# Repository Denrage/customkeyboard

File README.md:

# Custom Keyboard
## Planned Features
- ISO-Layout
- RGB per Key
- RGB Underglow
- TKL (80%)
- USB-C
- QMK
## Ressources
- JLCPCB - PCB Manfucaturer
- http://www.keyboard-layout-editor.com/#/
- https://github.com/jeroen94704/klepcbgen
- https://wiki.ai03.com/books/pcb-design/page/pcb-guide-part-1---preparations
- https://github.com/ruiqimao/keyboard-pcb-guide
## Needed Components (Will be more specific in the future)
- Resistors
- Diodes
- Key Switches
- (Key Caps)
- MCU
- Crystal/Clock
- USB-C Port
- RGB-LEDs
## Needed Tools
- Soldering Iron
- Soldering Paste
- Solder
- Hot Air Gun
- Flux
- Magnifying glass / microscope
- Fan

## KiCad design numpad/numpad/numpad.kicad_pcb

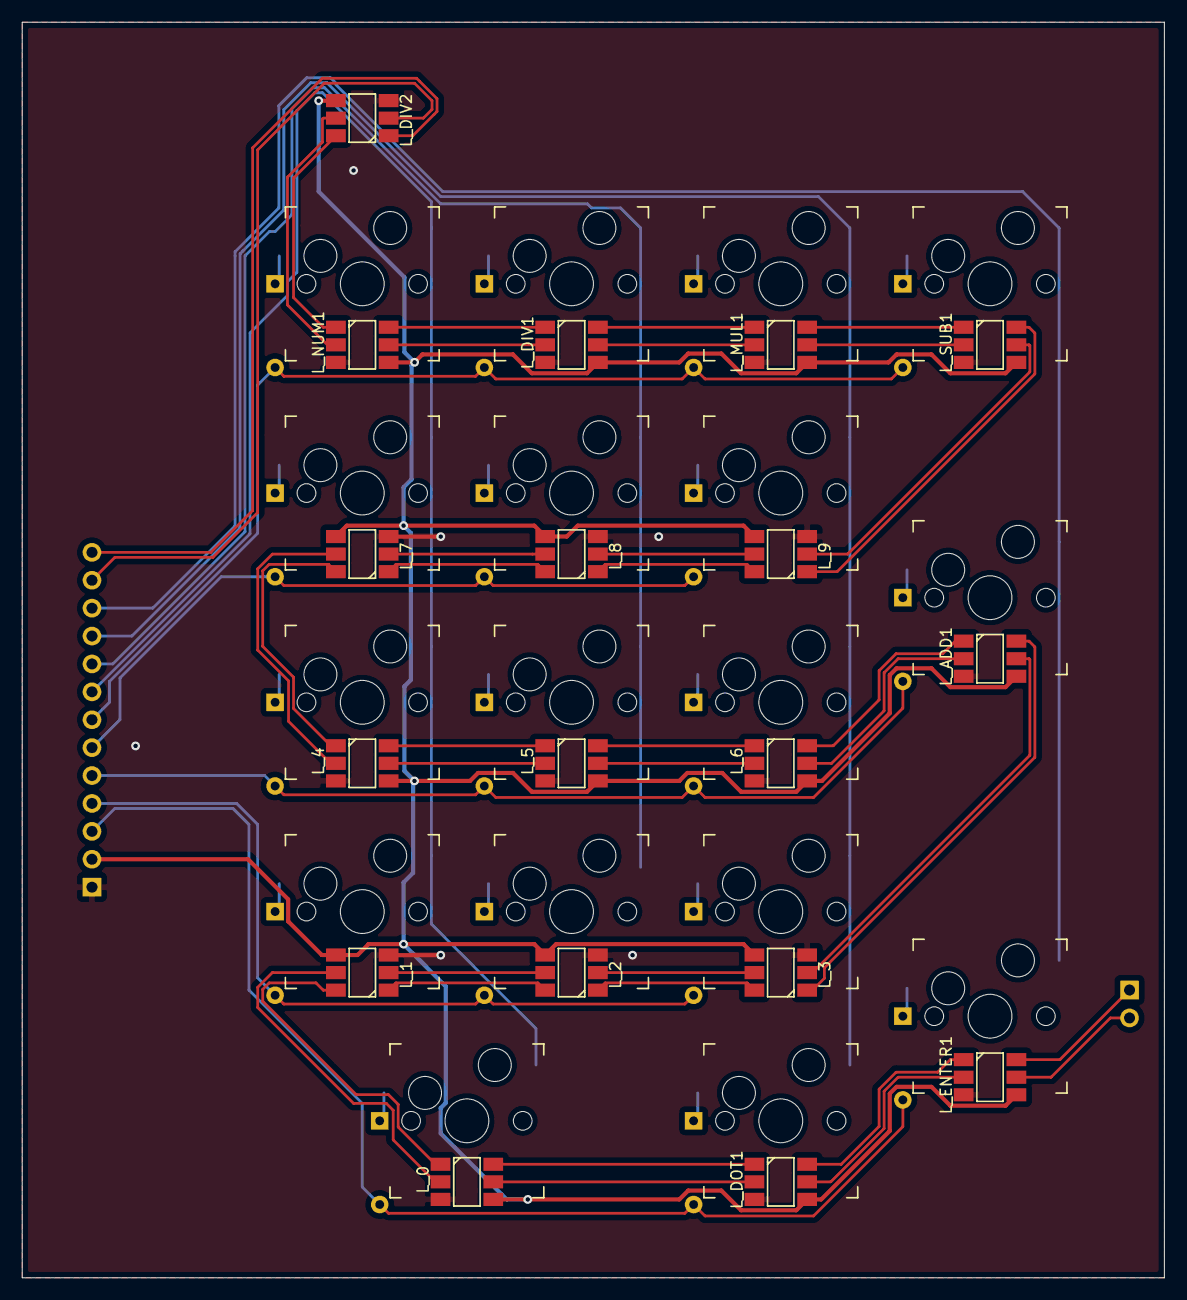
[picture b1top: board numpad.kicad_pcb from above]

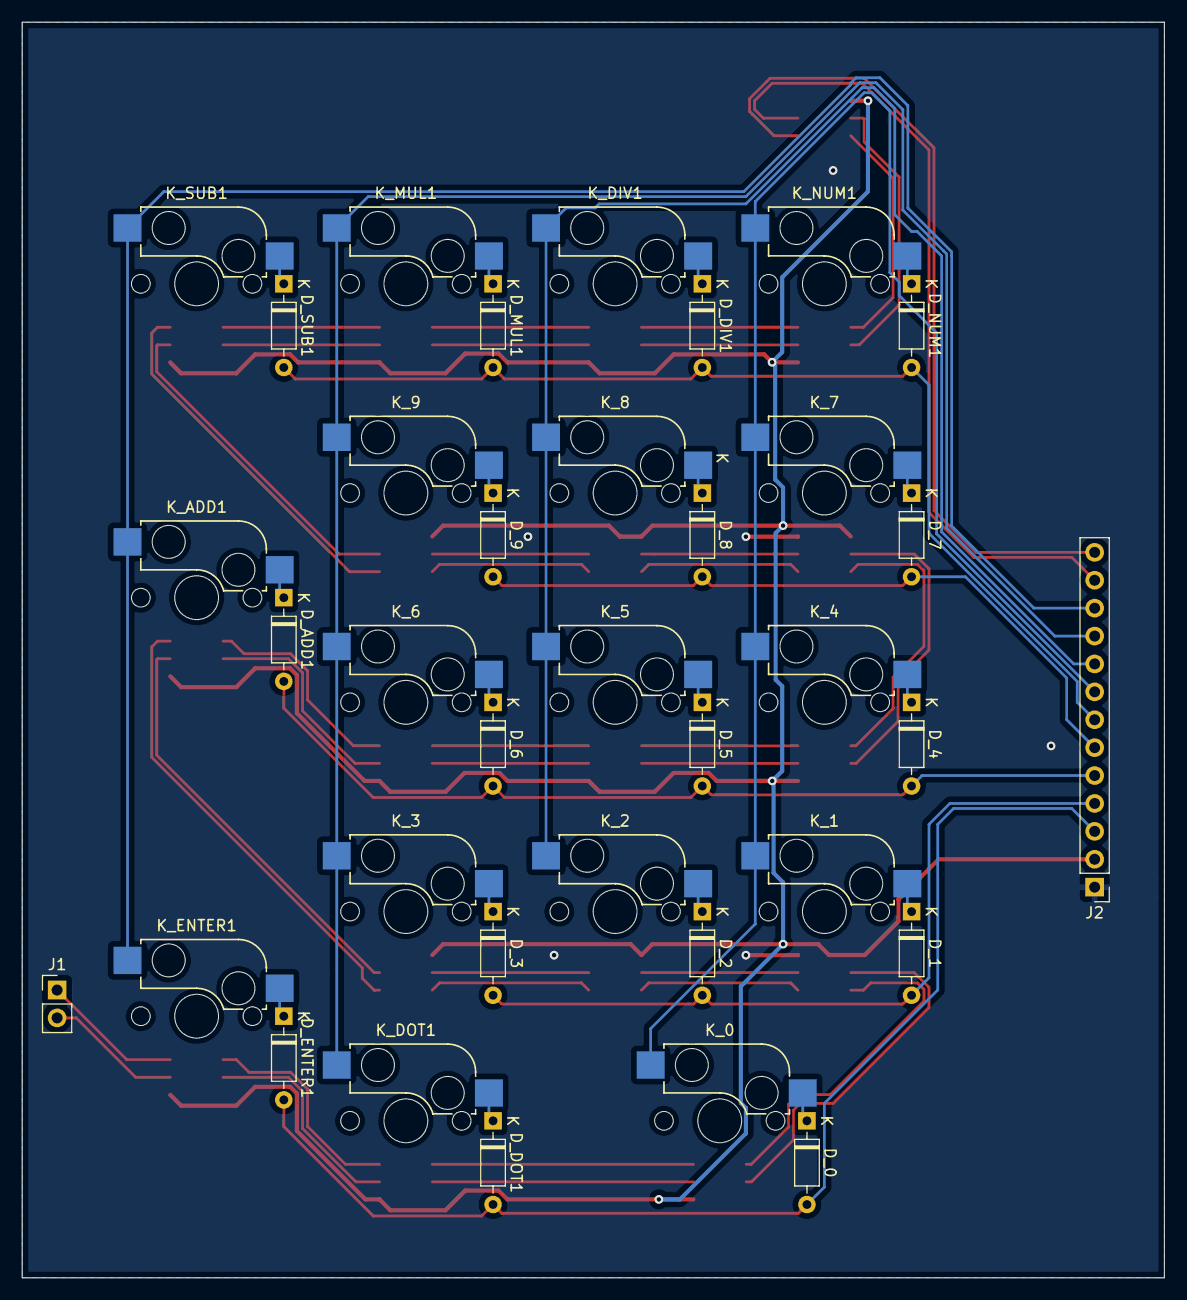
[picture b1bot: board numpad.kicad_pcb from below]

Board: 2 copper layers, 104.0 x 114.3 mm, 54 parts (19 on the bottom side), 66 nets.

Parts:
D_0, D_1, D_2, D_3, D_4, D_5, D_6, D_7, D_8, D_9: DIODE; D_DO-35_SOD27_P7.62mm_Horizontal
D_ADD1: DIODE; D_DO-35_SOD27_P7.62mm_Horizontal
D_DIV1: DIODE; D_DO-35_SOD27_P7.62mm_Horizontal
D_DOT1: DIODE; D_DO-35_SOD27_P7.62mm_Horizontal
D_ENTER1: DIODE; D_DO-35_SOD27_P7.62mm_Horizontal
D_MUL1: DIODE; D_DO-35_SOD27_P7.62mm_Horizontal
D_NUM1: DIODE; D_DO-35_SOD27_P7.62mm_Horizontal
D_SUB1: DIODE; D_DO-35_SOD27_P7.62mm_Horizontal
J1: Conn_01x02; PinHeader_1x02_P2.54mm_Vertical
J2: Conn_01x13; PinHeader_1x13_P2.54mm_Vertical
K_0, K_1, K_2, K_3, K_4, K_5, K_6, K_7, K_8, K_9: SW_DIP_x01; Kailh_socket_MX
K_ADD1: SW_DIP_x01; Kailh_socket_MX
K_DIV1: SW_DIP_x01; Kailh_socket_MX
K_DOT1: SW_DIP_x01; Kailh_socket_MX
K_ENTER1: SW_DIP_x01; Kailh_socket_MX
K_MUL1: SW_DIP_x01; Kailh_socket_MX
K_NUM1: SW_DIP_x01; Kailh_socket_MX
K_SUB1: SW_DIP_x01; Kailh_socket_MX
L_0, L_1, L_2, L_3, L_4, L_5, L_6, L_7, L_8, L_9: SK9822; APA102_hand_solder
L_ADD1: SK9822; APA102_hand_solder
L_DIV1, L_DIV2: SK9822; APA102_hand_solder
L_DOT1: SK9822; APA102_hand_solder
L_ENTER1: SK9822; APA102_hand_solder
L_MUL1: SK9822; APA102_hand_solder
L_NUM1: SK9822; APA102_hand_solder
L_SUB1: SK9822; APA102_hand_solder

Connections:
/Key Matrix/CIN: J2.12, L_DIV2.2
/Key Matrix/COL1: J2.8, K_0.1, K_1.1, K_4.1, K_7.1, K_NUM1.1
/Key Matrix/COL2: J2.9, K_2.1, K_5.1, K_8.1, K_DIV1.1
/Key Matrix/COL3: J2.10, K_3.1, K_6.1, K_9.1, K_DOT1.1, K_MUL1.1
/Key Matrix/COL4: J2.11, K_ADD1.1, K_ENTER1.1, K_SUB1.1
/Key Matrix/COUT: J1.2, L_ENTER1.5
/Key Matrix/DIN: J2.13, L_DIV2.1
/Key Matrix/DOUT: J1.1, L_ENTER1.6
/Key Matrix/ROW1: D_DIV1.2, D_MUL1.2, D_NUM1.2, D_SUB1.2, J2.7
/Key Matrix/ROW2: D_7.2, D_8.2, D_9.2, J2.6
/Key Matrix/ROW3: D_4.2, D_5.2, D_6.2, D_ADD1.2, J2.5
/Key Matrix/ROW4: D_1.2, D_2.2, D_3.2, J2.4
/Key Matrix/ROW5: D_0.2, D_DOT1.2, D_ENTER1.2, J2.3
/Key Matrix/VCC: J2.2, L_0.4, L_1.4, L_2.4, L_3.4, L_4.4, L_5.4, L_6.4, L_7.4, L_8.4, L_9.4, L_ADD1.4, L_DIV1.4, L_DIV2.4, L_DOT1.4, L_ENTER1.4, L_MUL1.4, L_NUM1.4, L_SUB1.4
GND: J2.1, L_0.3, L_1.3, L_2.3, L_3.3, L_4.3, L_5.3, L_6.3, L_7.3, L_8.3, L_9.3, L_ADD1.3, L_DIV1.3, L_DIV2.3, L_DOT1.3, L_ENTER1.3, L_MUL1.3, L_NUM1.3, L_SUB1.3
unnamed: D_0.1, K_0.2
unnamed: D_1.1, K_1.2
unnamed: D_2.1, K_2.2
unnamed: D_3.1, K_3.2
unnamed: D_4.1, K_4.2
unnamed: D_5.1, K_5.2
unnamed: D_6.1, K_6.2
unnamed: D_7.1, K_7.2
unnamed: D_8.1, K_8.2
unnamed: D_9.1, K_9.2
unnamed: D_ADD1.1, K_ADD1.2
unnamed: D_DIV1.1, K_DIV1.2
unnamed: D_DOT1.1, K_DOT1.2
unnamed: D_ENTER1.1, K_ENTER1.2
unnamed: D_MUL1.1, K_MUL1.2
unnamed: D_NUM1.1, K_NUM1.2
unnamed: D_SUB1.1, K_SUB1.2
unnamed: L_0.1, L_1.6
unnamed: L_0.2, L_1.5
unnamed: L_0.5, L_DOT1.2
unnamed: L_0.6, L_DOT1.1
unnamed: L_1.1, L_2.6
unnamed: L_1.2, L_2.5
unnamed: L_2.1, L_3.6
unnamed: L_2.2, L_3.5
unnamed: L_3.1, L_ADD1.6
unnamed: L_3.2, L_ADD1.5
unnamed: L_4.1, L_7.6
unnamed: L_4.2, L_7.5
unnamed: L_4.5, L_5.2
unnamed: L_4.6, L_5.1
unnamed: L_5.5, L_6.2
unnamed: L_5.6, L_6.1
unnamed: L_6.5, L_ADD1.2
unnamed: L_6.6, L_ADD1.1
unnamed: L_7.1, L_8.6
unnamed: L_7.2, L_8.5
unnamed: L_8.1, L_9.6
unnamed: L_8.2, L_9.5
unnamed: L_9.1, L_SUB1.6
unnamed: L_9.2, L_SUB1.5
unnamed: L_DIV1.1, L_NUM1.6
unnamed: L_DIV1.2, L_NUM1.5
unnamed: L_DIV1.5, L_MUL1.2
unnamed: L_DIV1.6, L_MUL1.1
unnamed: L_DIV2.5, L_NUM1.2
unnamed: L_DIV2.6, L_NUM1.1
unnamed: L_DOT1.5, L_ENTER1.2
unnamed: L_DOT1.6, L_ENTER1.1
unnamed: L_MUL1.5, L_SUB1.2
unnamed: L_MUL1.6, L_SUB1.1

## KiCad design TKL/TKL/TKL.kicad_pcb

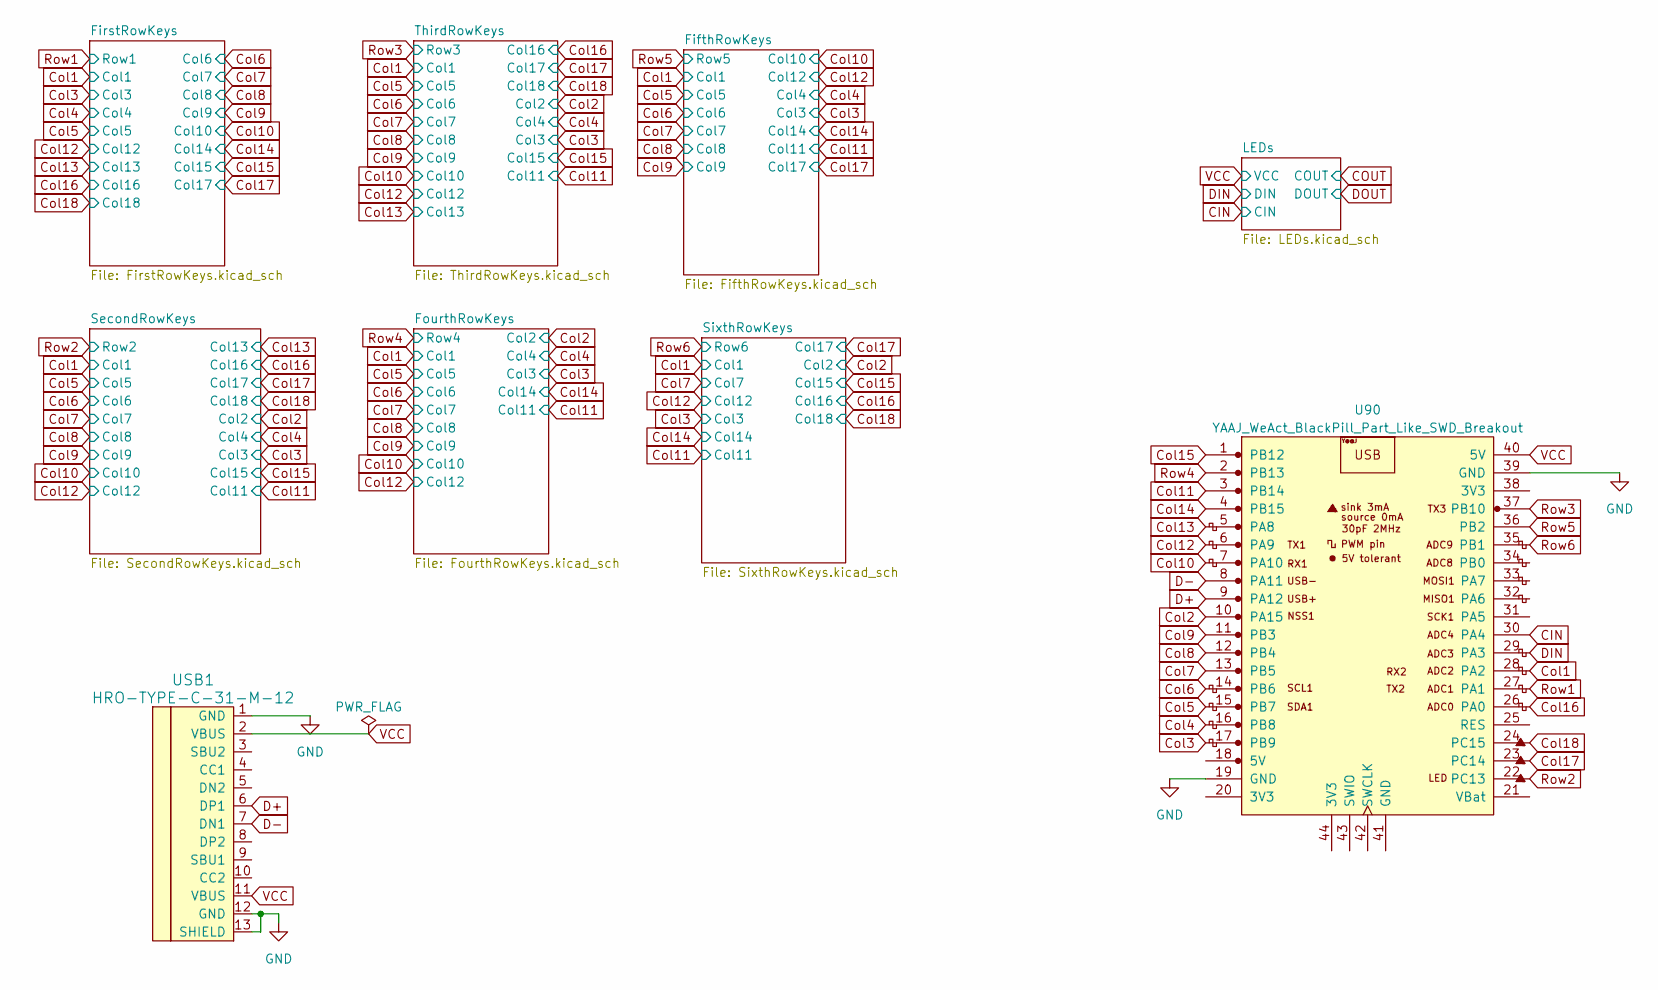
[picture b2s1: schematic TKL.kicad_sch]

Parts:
U90: YAAJ_WeAct_BlackPill_Part_Like_SWD_Breakout; YAAJ_WeAct_BlackPill_2
USB1: HRO-TYPE-C-31-M-12; HRO-TYPE-C-31-M-12-Assembly

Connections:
unnamed: U90.8 (PA11), USB1.7 (DN1)
unnamed: U90.9 (PA12), USB1.6 (DP1)
unnamed: U90.19 (GND), U90.39 (GND), USB1.1 (GND), USB1.12 (GND), USB1.13 (SHIELD)
unnamed: U90.40 (5V), USB1.2 (VBUS), USB1.11 (VBUS)

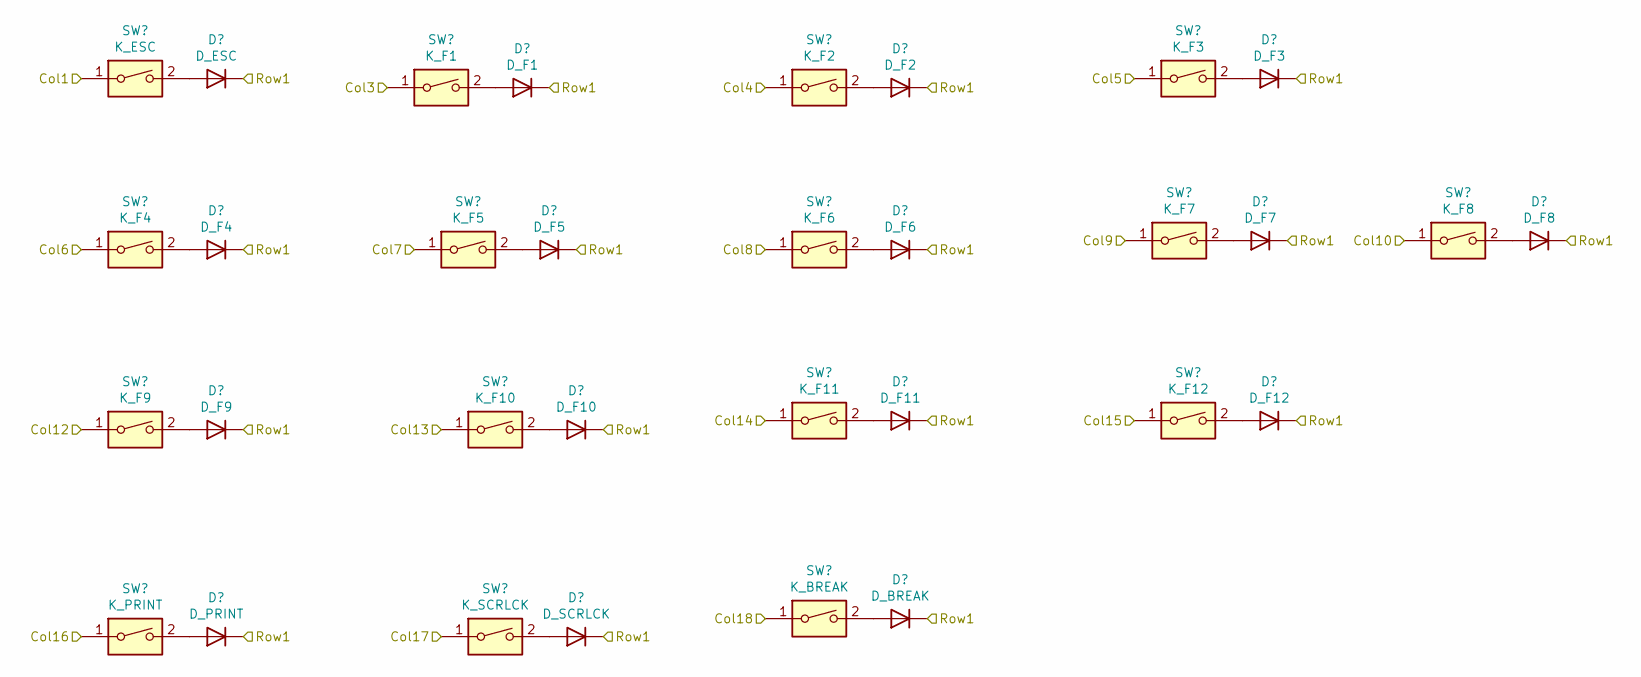
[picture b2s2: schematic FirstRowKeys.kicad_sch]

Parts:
D1: D_ESC; D_DO-35_SOD27_P7.62mm_Horizontal
D2: D_F4; D_DO-35_SOD27_P7.62mm_Horizontal
D3: D_F9; D_DO-35_SOD27_P7.62mm_Horizontal
D4: D_PRINT; D_DO-35_SOD27_P7.62mm_Horizontal
D5: D_F1; D_DO-35_SOD27_P7.62mm_Horizontal
D6: D_F5; D_DO-35_SOD27_P7.62mm_Horizontal
D7: D_F10; D_DO-35_SOD27_P7.62mm_Horizontal
D8: D_SCRLCK; D_DO-35_SOD27_P7.62mm_Horizontal
D9: D_F2; D_DO-35_SOD27_P7.62mm_Horizontal
D10: D_F6; D_DO-35_SOD27_P7.62mm_Horizontal
D11: D_F11; D_DO-35_SOD27_P7.62mm_Horizontal
D12: D_BREAK; D_DO-35_SOD27_P7.62mm_Horizontal
D13: D_F7; D_DO-35_SOD27_P7.62mm_Horizontal
D14: D_F3; D_DO-35_SOD27_P7.62mm_Horizontal
D15: D_F12; D_DO-35_SOD27_P7.62mm_Horizontal
D16: D_F8; D_DO-35_SOD27_P7.62mm_Horizontal
SW1: K_ESC; Kailh_socket_MX
SW2: K_F4; Kailh_socket_MX
SW3: K_F9; Kailh_socket_MX
SW4: K_PRINT; Kailh_socket_MX
SW5: K_F1; Kailh_socket_MX
SW6: K_F5; Kailh_socket_MX
SW7: K_F10; Kailh_socket_MX
SW8: K_SCRLCK; Kailh_socket_MX
SW9: K_F2; Kailh_socket_MX
SW10: K_F6; Kailh_socket_MX
SW11: K_F11; Kailh_socket_MX
SW12: K_BREAK; Kailh_socket_MX
SW13: K_F7; Kailh_socket_MX
SW14: K_F3; Kailh_socket_MX
SW15: K_F12; Kailh_socket_MX
SW16: K_F8; Kailh_socket_MX

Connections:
Col1: SW1.1; also elsewhere on the board
Col3: SW5.1; also elsewhere on the board
Col4: SW9.1; also elsewhere on the board
Col5: SW14.1; also elsewhere on the board
Col6: SW2.1; also elsewhere on the board
Col7: SW6.1; also elsewhere on the board
Col8: SW10.1; also elsewhere on the board
Col9: SW13.1; also elsewhere on the board
Col10: SW16.1; also elsewhere on the board
Col12: SW3.1; also elsewhere on the board
Col13: SW7.1; also elsewhere on the board
Col14: SW11.1; also elsewhere on the board
Col15: SW15.1; also elsewhere on the board
Col16: SW4.1; also elsewhere on the board
Col17: SW8.1; also elsewhere on the board
Col18: SW12.1; also elsewhere on the board
unnamed: D1.2 (A), SW1.2
unnamed: D2.2 (A), SW2.2
unnamed: D3.2 (A), SW3.2
unnamed: D4.2 (A), SW4.2
unnamed: D5.2 (A), SW5.2
unnamed: D6.2 (A), SW6.2
unnamed: D7.2 (A), SW7.2
unnamed: D8.2 (A), SW8.2
unnamed: D9.2 (A), SW9.2
unnamed: D10.2 (A), SW10.2
unnamed: D11.2 (A), SW11.2
unnamed: D12.2 (A), SW12.2
unnamed: D13.2 (A), SW13.2
unnamed: D14.2 (A), SW14.2
unnamed: D15.2 (A), SW15.2
unnamed: D16.2 (A), SW16.2
Row1: D1.1 (K), D2.1 (K), D3.1 (K), D4.1 (K), D5.1 (K), D6.1 (K), D7.1 (K), D8.1 (K), D9.1 (K), D10.1 (K), D11.1 (K), D12.1 (K), D13.1 (K), D14.1 (K), D15.1 (K), D16.1 (K)

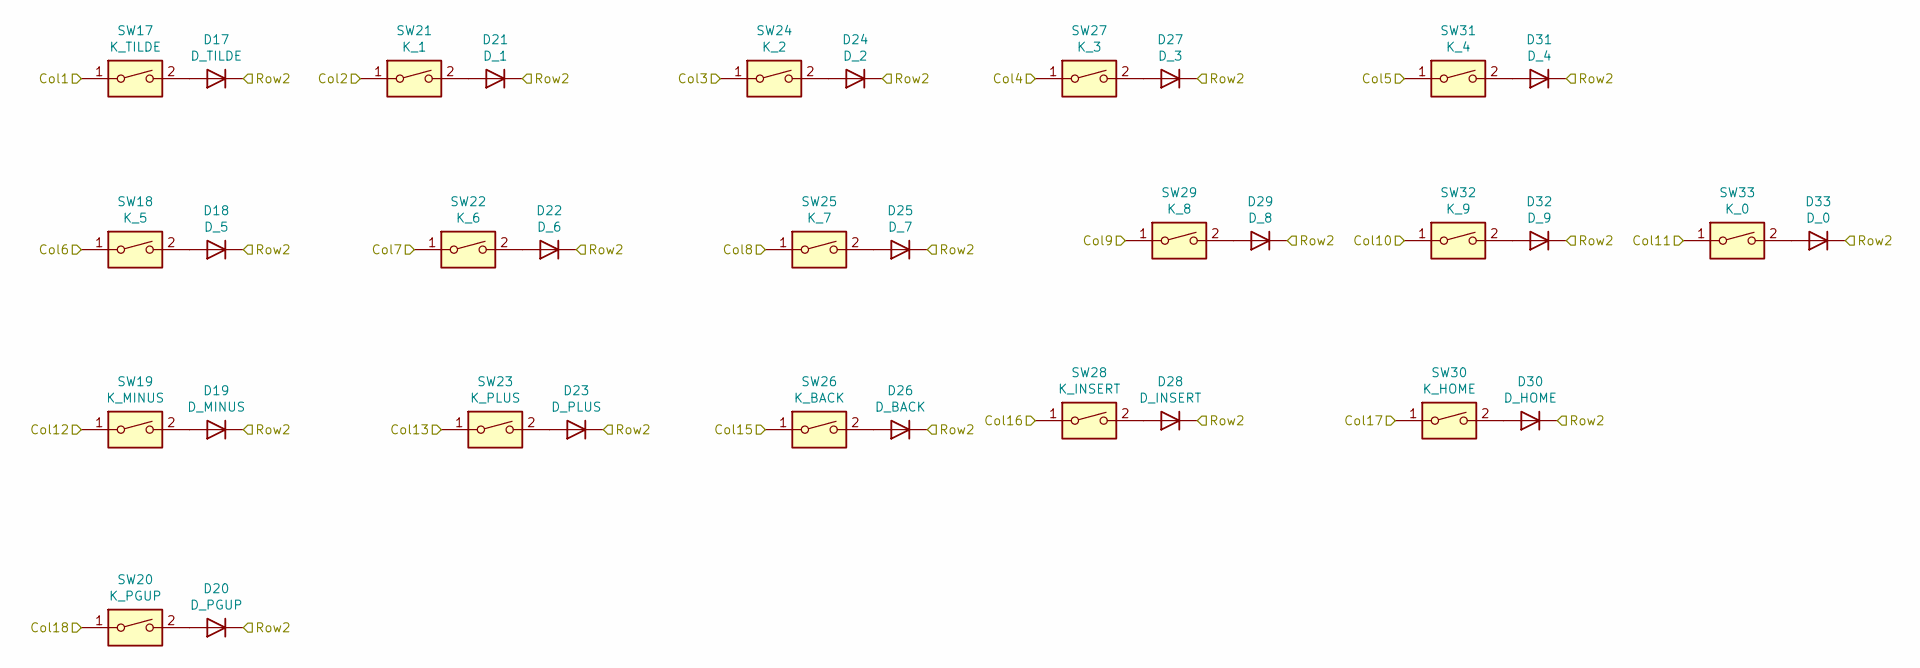
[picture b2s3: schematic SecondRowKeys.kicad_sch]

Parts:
D17: D_TILDE; D_DO-35_SOD27_P7.62mm_Horizontal
D18: D_5; D_DO-35_SOD27_P7.62mm_Horizontal
D19: D_MINUS; D_DO-35_SOD27_P7.62mm_Horizontal
D20: D_PGUP; D_DO-35_SOD27_P7.62mm_Horizontal
D21: D_1; D_DO-35_SOD27_P7.62mm_Horizontal
D22: D_6; D_DO-35_SOD27_P7.62mm_Horizontal
D23: D_PLUS; D_DO-35_SOD27_P7.62mm_Horizontal
D24: D_2; D_DO-35_SOD27_P7.62mm_Horizontal
D25: D_7; D_DO-35_SOD27_P7.62mm_Horizontal
D26: D_BACK; D_DO-35_SOD27_P7.62mm_Horizontal
D27: D_3; D_DO-35_SOD27_P7.62mm_Horizontal
D28: D_INSERT; D_DO-35_SOD27_P7.62mm_Horizontal
D29: D_8; D_DO-35_SOD27_P7.62mm_Horizontal
D30: D_HOME; D_DO-35_SOD27_P7.62mm_Horizontal
D31: D_4; D_DO-35_SOD27_P7.62mm_Horizontal
D32: D_9; D_DO-35_SOD27_P7.62mm_Horizontal
D33: D_0; D_DO-35_SOD27_P7.62mm_Horizontal
SW17: K_TILDE; Kailh_socket_MX
SW18: K_5; Kailh_socket_MX
SW19: K_MINUS; Kailh_socket_MX
SW20: K_PGUP; Kailh_socket_MX
SW21: K_1; Kailh_socket_MX
SW22: K_6; Kailh_socket_MX
SW23: K_PLUS; Kailh_socket_MX
SW24: K_2; Kailh_socket_MX
SW25: K_7; Kailh_socket_MX
SW26: K_BACK; Kailh_socket_MX
SW27: K_3; Kailh_socket_MX
SW28: K_INSERT; Kailh_socket_MX
SW29: K_8; Kailh_socket_MX
SW30: K_HOME; Kailh_socket_MX
SW31: K_4; Kailh_socket_MX
SW32: K_9; Kailh_socket_MX
SW33: K_0; Kailh_socket_MX

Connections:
Col1: SW17.1; also elsewhere on the board
Col2: SW21.1; also elsewhere on the board
Col3: SW24.1; also elsewhere on the board
Col4: SW27.1; also elsewhere on the board
Col5: SW31.1; also elsewhere on the board
Col6: SW18.1; also elsewhere on the board
Col7: SW22.1; also elsewhere on the board
Col8: SW25.1; also elsewhere on the board
Col9: SW29.1; also elsewhere on the board
Col10: SW32.1; also elsewhere on the board
Col11: SW33.1; also elsewhere on the board
Col12: SW19.1; also elsewhere on the board
Col13: SW23.1; also elsewhere on the board
Col15: SW26.1; also elsewhere on the board
Col16: SW28.1; also elsewhere on the board
Col17: SW30.1; also elsewhere on the board
Col18: SW20.1; also elsewhere on the board
unnamed: D17.2 (A), SW17.2
unnamed: D18.2 (A), SW18.2
unnamed: D19.2 (A), SW19.2
unnamed: D20.2 (A), SW20.2
unnamed: D21.2 (A), SW21.2
unnamed: D22.2 (A), SW22.2
unnamed: D23.2 (A), SW23.2
unnamed: D24.2 (A), SW24.2
unnamed: D25.2 (A), SW25.2
unnamed: D26.2 (A), SW26.2
unnamed: D27.2 (A), SW27.2
unnamed: D28.2 (A), SW28.2
unnamed: D29.2 (A), SW29.2
unnamed: D30.2 (A), SW30.2
unnamed: D31.2 (A), SW31.2
unnamed: D32.2 (A), SW32.2
unnamed: D33.2 (A), SW33.2
Row2: D17.1 (K), D18.1 (K), D19.1 (K), D20.1 (K), D21.1 (K), D22.1 (K), D23.1 (K), D24.1 (K), D25.1 (K), D26.1 (K), D27.1 (K), D28.1 (K), D29.1 (K), D30.1 (K), D31.1 (K), D32.1 (K), D33.1 (K)

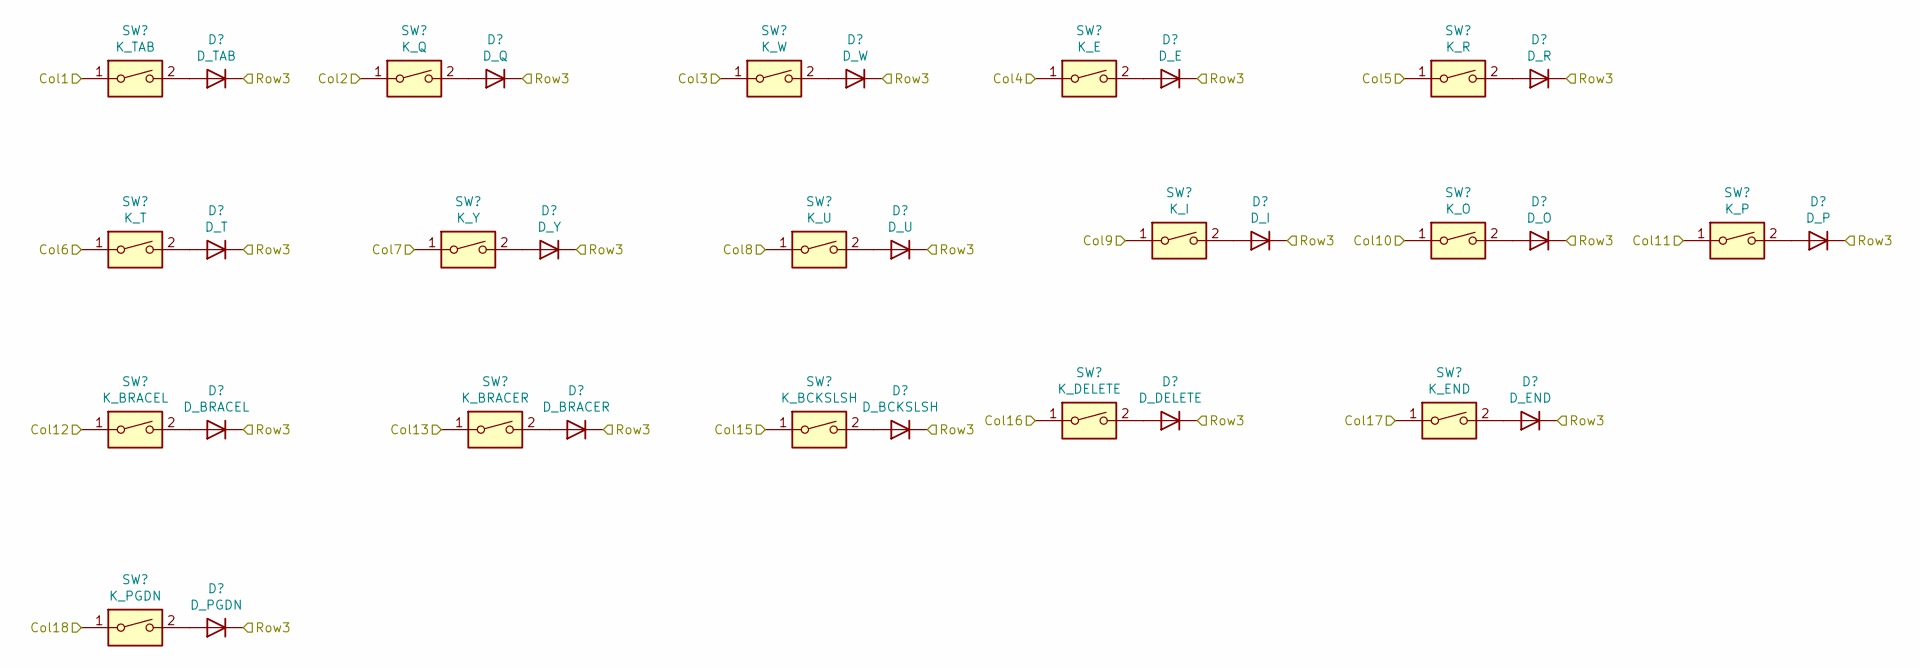
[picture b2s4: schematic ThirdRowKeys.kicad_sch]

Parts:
D34: D_TAB; D_DO-35_SOD27_P7.62mm_Horizontal
D35: D_T; D_DO-35_SOD27_P7.62mm_Horizontal
D36: D_BRACEL; D_DO-35_SOD27_P7.62mm_Horizontal
D37: D_PGDN; D_DO-35_SOD27_P7.62mm_Horizontal
D38: D_Q; D_DO-35_SOD27_P7.62mm_Horizontal
D39: D_Y; D_DO-35_SOD27_P7.62mm_Horizontal
D40: D_BRACER; D_DO-35_SOD27_P7.62mm_Horizontal
D41: D_W; D_DO-35_SOD27_P7.62mm_Horizontal
D42: D_U; D_DO-35_SOD27_P7.62mm_Horizontal
D43: D_BCKSLSH; D_DO-35_SOD27_P7.62mm_Horizontal
D44: D_E; D_DO-35_SOD27_P7.62mm_Horizontal
D45: D_DELETE; D_DO-35_SOD27_P7.62mm_Horizontal
D46: D_I; D_DO-35_SOD27_P7.62mm_Horizontal
D47: D_END; D_DO-35_SOD27_P7.62mm_Horizontal
D48: D_R; D_DO-35_SOD27_P7.62mm_Horizontal
D49: D_O; D_DO-35_SOD27_P7.62mm_Horizontal
D50: D_P; D_DO-35_SOD27_P7.62mm_Horizontal
SW34: K_TAB; Kailh_socket_MX
SW35: K_T; Kailh_socket_MX
SW36: K_BRACEL; Kailh_socket_MX
SW37: K_PGDN; Kailh_socket_MX
SW38: K_Q; Kailh_socket_MX
SW39: K_Y; Kailh_socket_MX
SW40: K_BRACER; Kailh_socket_MX
SW41: K_W; Kailh_socket_MX
SW42: K_U; Kailh_socket_MX
SW43: K_BCKSLSH; Kailh_socket_MX
SW44: K_E; Kailh_socket_MX
SW45: K_DELETE; Kailh_socket_MX
SW46: K_I; Kailh_socket_MX
SW47: K_END; Kailh_socket_MX
SW48: K_R; Kailh_socket_MX
SW49: K_O; Kailh_socket_MX
SW50: K_P; Kailh_socket_MX

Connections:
/ThirdRowKeys/Col11: SW50.1
Col1: SW34.1; also elsewhere on the board
Col2: SW38.1; also elsewhere on the board
Col3: SW41.1; also elsewhere on the board
Col4: SW44.1; also elsewhere on the board
Col5: SW48.1; also elsewhere on the board
Col6: SW35.1; also elsewhere on the board
Col7: SW39.1; also elsewhere on the board
Col8: SW42.1; also elsewhere on the board
Col9: SW46.1; also elsewhere on the board
Col10: SW49.1; also elsewhere on the board
Col12: SW36.1; also elsewhere on the board
Col13: SW40.1; also elsewhere on the board
Col15: SW43.1; also elsewhere on the board
Col16: SW45.1; also elsewhere on the board
Col17: SW47.1; also elsewhere on the board
Col18: SW37.1; also elsewhere on the board
unnamed: D34.2 (A), SW34.2
unnamed: D35.2 (A), SW35.2
unnamed: D36.2 (A), SW36.2
unnamed: D37.2 (A), SW37.2
unnamed: D38.2 (A), SW38.2
unnamed: D39.2 (A), SW39.2
unnamed: D40.2 (A), SW40.2
unnamed: D41.2 (A), SW41.2
unnamed: D42.2 (A), SW42.2
unnamed: D43.2 (A), SW43.2
unnamed: D44.2 (A), SW44.2
unnamed: D45.2 (A), SW45.2
unnamed: D46.2 (A), SW46.2
unnamed: D47.2 (A), SW47.2
unnamed: D48.2 (A), SW48.2
unnamed: D49.2 (A), SW49.2
unnamed: D50.2 (A), SW50.2
Row3: D34.1 (K), D35.1 (K), D36.1 (K), D37.1 (K), D38.1 (K), D39.1 (K), D40.1 (K), D41.1 (K), D42.1 (K), D43.1 (K), D44.1 (K), D45.1 (K), D46.1 (K), D47.1 (K), D48.1 (K), D49.1 (K), D50.1 (K)

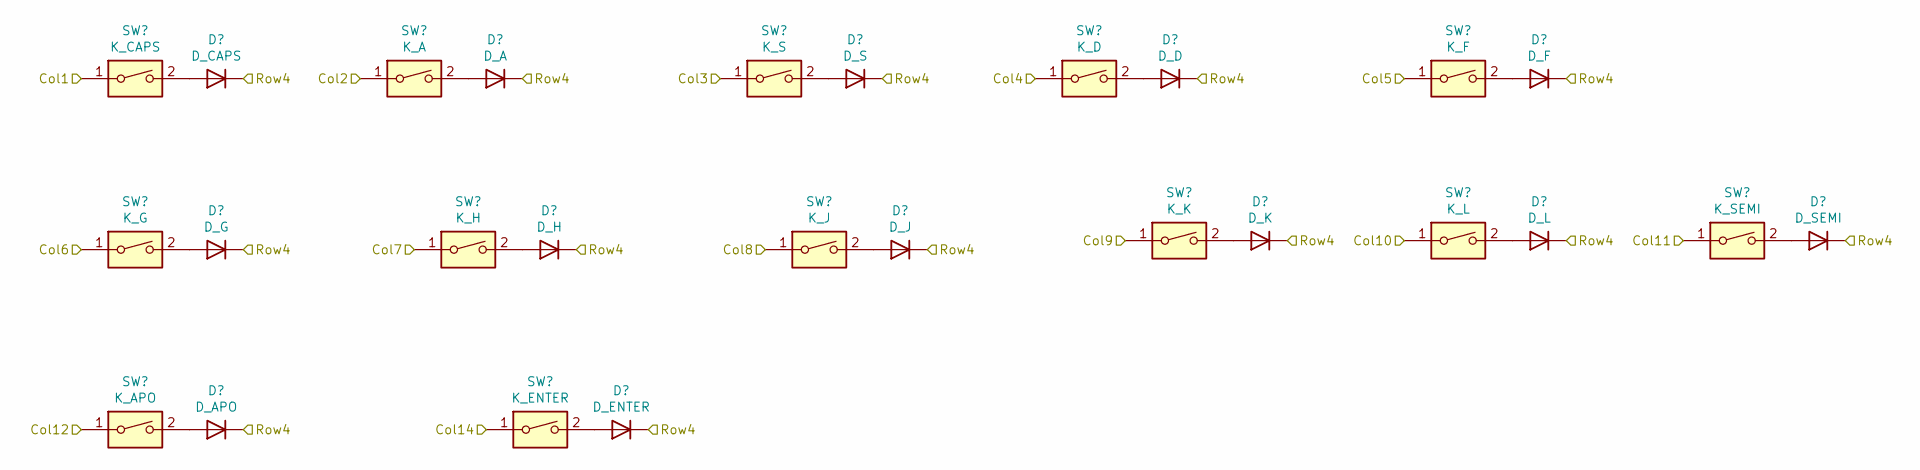
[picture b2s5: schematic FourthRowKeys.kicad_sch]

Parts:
D51: D_CAPS; D_DO-35_SOD27_P7.62mm_Horizontal
D52: D_G; D_DO-35_SOD27_P7.62mm_Horizontal
D53: D_APO; D_DO-35_SOD27_P7.62mm_Horizontal
D54: D_A; D_DO-35_SOD27_P7.62mm_Horizontal
D55: D_H; D_DO-35_SOD27_P7.62mm_Horizontal
D56: D_ENTER; D_DO-35_SOD27_P7.62mm_Horizontal
D57: D_S; D_DO-35_SOD27_P7.62mm_Horizontal
D58: D_J; D_DO-35_SOD27_P7.62mm_Horizontal
D59: D_D; D_DO-35_SOD27_P7.62mm_Horizontal
D60: D_K; D_DO-35_SOD27_P7.62mm_Horizontal
D61: D_F; D_DO-35_SOD27_P7.62mm_Horizontal
D62: D_L; D_DO-35_SOD27_P7.62mm_Horizontal
D63: D_SEMI; D_DO-35_SOD27_P7.62mm_Horizontal
SW51: K_CAPS; Kailh_socket_MX
SW52: K_G; Kailh_socket_MX
SW53: K_APO; Kailh_socket_MX
SW54: K_A; Kailh_socket_MX
SW55: K_H; Kailh_socket_MX
SW56: K_ENTER; Kailh_socket_MX
SW57: K_S; Kailh_socket_MX
SW58: K_J; Kailh_socket_MX
SW59: K_D; Kailh_socket_MX
SW60: K_K; Kailh_socket_MX
SW61: K_F; Kailh_socket_MX
SW62: K_L; Kailh_socket_MX
SW63: K_SEMI; Kailh_socket_MX

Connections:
Col1: SW51.1; also elsewhere on the board
Col2: SW54.1; also elsewhere on the board
Col3: SW57.1; also elsewhere on the board
Col4: SW59.1; also elsewhere on the board
Col5: SW61.1; also elsewhere on the board
Col6: SW52.1; also elsewhere on the board
Col7: SW55.1; also elsewhere on the board
Col8: SW58.1; also elsewhere on the board
Col9: SW60.1; also elsewhere on the board
Col10: SW62.1; also elsewhere on the board
Col11: SW63.1; also elsewhere on the board
Col12: SW53.1; also elsewhere on the board
Col14: SW56.1; also elsewhere on the board
unnamed: D51.2 (A), SW51.2
unnamed: D52.2 (A), SW52.2
unnamed: D53.2 (A), SW53.2
unnamed: D54.2 (A), SW54.2
unnamed: D55.2 (A), SW55.2
unnamed: D56.2 (A), SW56.2
unnamed: D57.2 (A), SW57.2
unnamed: D58.2 (A), SW58.2
unnamed: D59.2 (A), SW59.2
unnamed: D60.2 (A), SW60.2
unnamed: D61.2 (A), SW61.2
unnamed: D62.2 (A), SW62.2
unnamed: D63.2 (A), SW63.2
Row4: D51.1 (K), D52.1 (K), D53.1 (K), D54.1 (K), D55.1 (K), D56.1 (K), D57.1 (K), D58.1 (K), D59.1 (K), D60.1 (K), D61.1 (K), D62.1 (K), D63.1 (K)

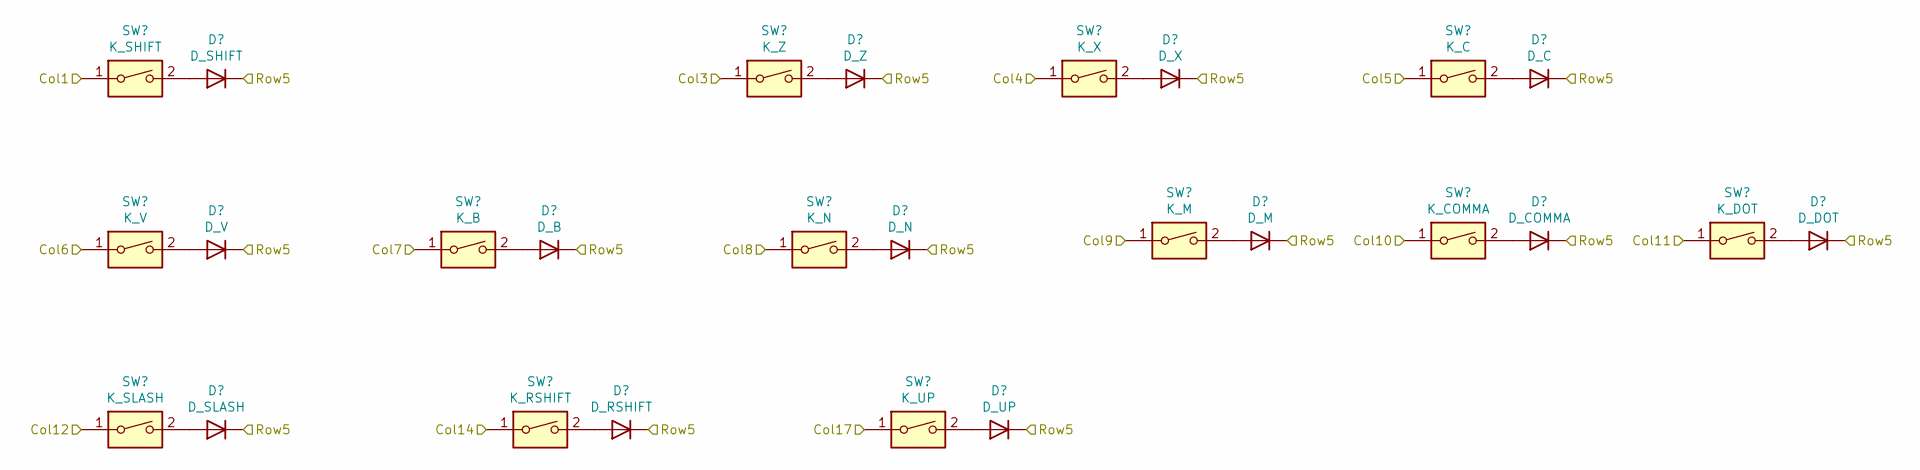
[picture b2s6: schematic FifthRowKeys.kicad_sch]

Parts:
D64: D_SHIFT; D_DO-35_SOD27_P7.62mm_Horizontal
D65: D_V; D_DO-35_SOD27_P7.62mm_Horizontal
D66: D_SLASH; D_DO-35_SOD27_P7.62mm_Horizontal
D67: D_B; D_DO-35_SOD27_P7.62mm_Horizontal
D68: D_RSHIFT; D_DO-35_SOD27_P7.62mm_Horizontal
D69: D_Z; D_DO-35_SOD27_P7.62mm_Horizontal
D70: D_N; D_DO-35_SOD27_P7.62mm_Horizontal
D71: D_UP; D_DO-35_SOD27_P7.62mm_Horizontal
D72: D_X; D_DO-35_SOD27_P7.62mm_Horizontal
D73: D_M; D_DO-35_SOD27_P7.62mm_Horizontal
D74: D_C; D_DO-35_SOD27_P7.62mm_Horizontal
D75: D_COMMA; D_DO-35_SOD27_P7.62mm_Horizontal
D76: D_DOT; D_DO-35_SOD27_P7.62mm_Horizontal
SW64: K_SHIFT; Kailh_socket_MX
SW65: K_V; Kailh_socket_MX
SW66: K_SLASH; Kailh_socket_MX
SW67: K_B; Kailh_socket_MX
SW68: K_RSHIFT; Kailh_socket_MX
SW69: K_Z; Kailh_socket_MX
SW70: K_N; Kailh_socket_MX
SW71: K_UP; Kailh_socket_MX
SW72: K_X; Kailh_socket_MX
SW73: K_M; Kailh_socket_MX
SW74: K_C; Kailh_socket_MX
SW75: K_COMMA; Kailh_socket_MX
SW76: K_DOT; Kailh_socket_MX

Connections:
Col1: SW64.1; also elsewhere on the board
Col3: SW69.1; also elsewhere on the board
Col4: SW72.1; also elsewhere on the board
Col5: SW74.1; also elsewhere on the board
Col6: SW65.1; also elsewhere on the board
Col7: SW67.1; also elsewhere on the board
Col8: SW70.1; also elsewhere on the board
Col9: SW73.1; also elsewhere on the board
Col10: SW75.1; also elsewhere on the board
Col11: SW76.1; also elsewhere on the board
Col12: SW66.1; also elsewhere on the board
Col14: SW68.1; also elsewhere on the board
Col17: SW71.1; also elsewhere on the board
unnamed: D64.2 (A), SW64.2
unnamed: D65.2 (A), SW65.2
unnamed: D66.2 (A), SW66.2
unnamed: D67.2 (A), SW67.2
unnamed: D68.2 (A), SW68.2
unnamed: D69.2 (A), SW69.2
unnamed: D70.2 (A), SW70.2
unnamed: D71.2 (A), SW71.2
unnamed: D72.2 (A), SW72.2
unnamed: D73.2 (A), SW73.2
unnamed: D74.2 (A), SW74.2
unnamed: D75.2 (A), SW75.2
unnamed: D76.2 (A), SW76.2
Row5: D64.1 (K), D65.1 (K), D66.1 (K), D67.1 (K), D68.1 (K), D69.1 (K), D70.1 (K), D71.1 (K), D72.1 (K), D73.1 (K), D74.1 (K), D75.1 (K), D76.1 (K)

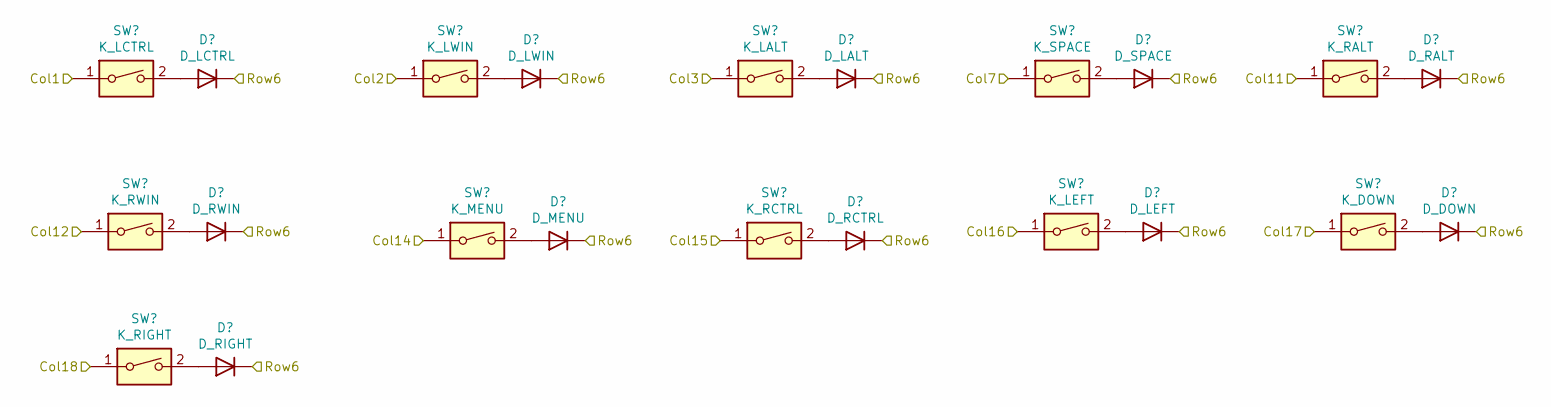
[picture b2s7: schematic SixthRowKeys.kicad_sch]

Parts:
D77: D_LCTRL; D_DO-35_SOD27_P7.62mm_Horizontal
D78: D_RWIN; D_DO-35_SOD27_P7.62mm_Horizontal
D79: D_RIGHT; D_DO-35_SOD27_P7.62mm_Horizontal
D80: D_LWIN; D_DO-35_SOD27_P7.62mm_Horizontal
D81: D_MENU; D_DO-35_SOD27_P7.62mm_Horizontal
D82: D_LALT; D_DO-35_SOD27_P7.62mm_Horizontal
D83: D_RCTRL; D_DO-35_SOD27_P7.62mm_Horizontal
D84: D_SPACE; D_DO-35_SOD27_P7.62mm_Horizontal
D85: D_LEFT; D_DO-35_SOD27_P7.62mm_Horizontal
D86: D_RALT; D_DO-35_SOD27_P7.62mm_Horizontal
D87: D_DOWN; D_DO-35_SOD27_P7.62mm_Horizontal
SW77: K_LCTRL; Kailh_socket_MX
SW78: K_RWIN; Kailh_socket_MX
SW79: K_RIGHT; Kailh_socket_MX
SW80: K_LWIN; Kailh_socket_MX
SW81: K_MENU; Kailh_socket_MX
SW82: K_LALT; Kailh_socket_MX
SW83: K_RCTRL; Kailh_socket_MX
SW84: K_SPACE; Kailh_socket_MX
SW85: K_LEFT; Kailh_socket_MX
SW86: K_RALT; Kailh_socket_MX
SW87: K_DOWN; Kailh_socket_MX

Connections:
Col1: SW77.1; also elsewhere on the board
Col2: SW80.1; also elsewhere on the board
Col3: SW82.1; also elsewhere on the board
Col11: SW86.1; also elsewhere on the board
Col12: SW78.1; also elsewhere on the board
Col14: SW81.1; also elsewhere on the board
Col15: SW83.1; also elsewhere on the board
Col16: SW85.1; also elsewhere on the board
Col17: SW87.1; also elsewhere on the board
Col18: SW79.1; also elsewhere on the board
unnamed: D77.2 (A), SW77.2
unnamed: D78.2 (A), SW78.2
unnamed: D79.2 (A), SW79.2
unnamed: D80.2 (A), SW80.2
unnamed: D81.2 (A), SW81.2
unnamed: D82.2 (A), SW82.2
unnamed: D83.2 (A), SW83.2
unnamed: D84.2 (A), SW84.2
unnamed: D85.2 (A), SW85.2
unnamed: D86.2 (A), SW86.2
unnamed: D87.2 (A), SW87.2
Row6: D77.1 (K), D78.1 (K), D79.1 (K), D80.1 (K), D81.1 (K), D82.1 (K), D83.1 (K), D84.1 (K), D85.1 (K), D86.1 (K), D87.1 (K)
